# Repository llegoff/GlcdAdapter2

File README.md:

Smoothieboard-glcd-adapter v2
=============================
[See documentation on smoothiware.org](http://smoothieware.org/rrdglcdadapter)

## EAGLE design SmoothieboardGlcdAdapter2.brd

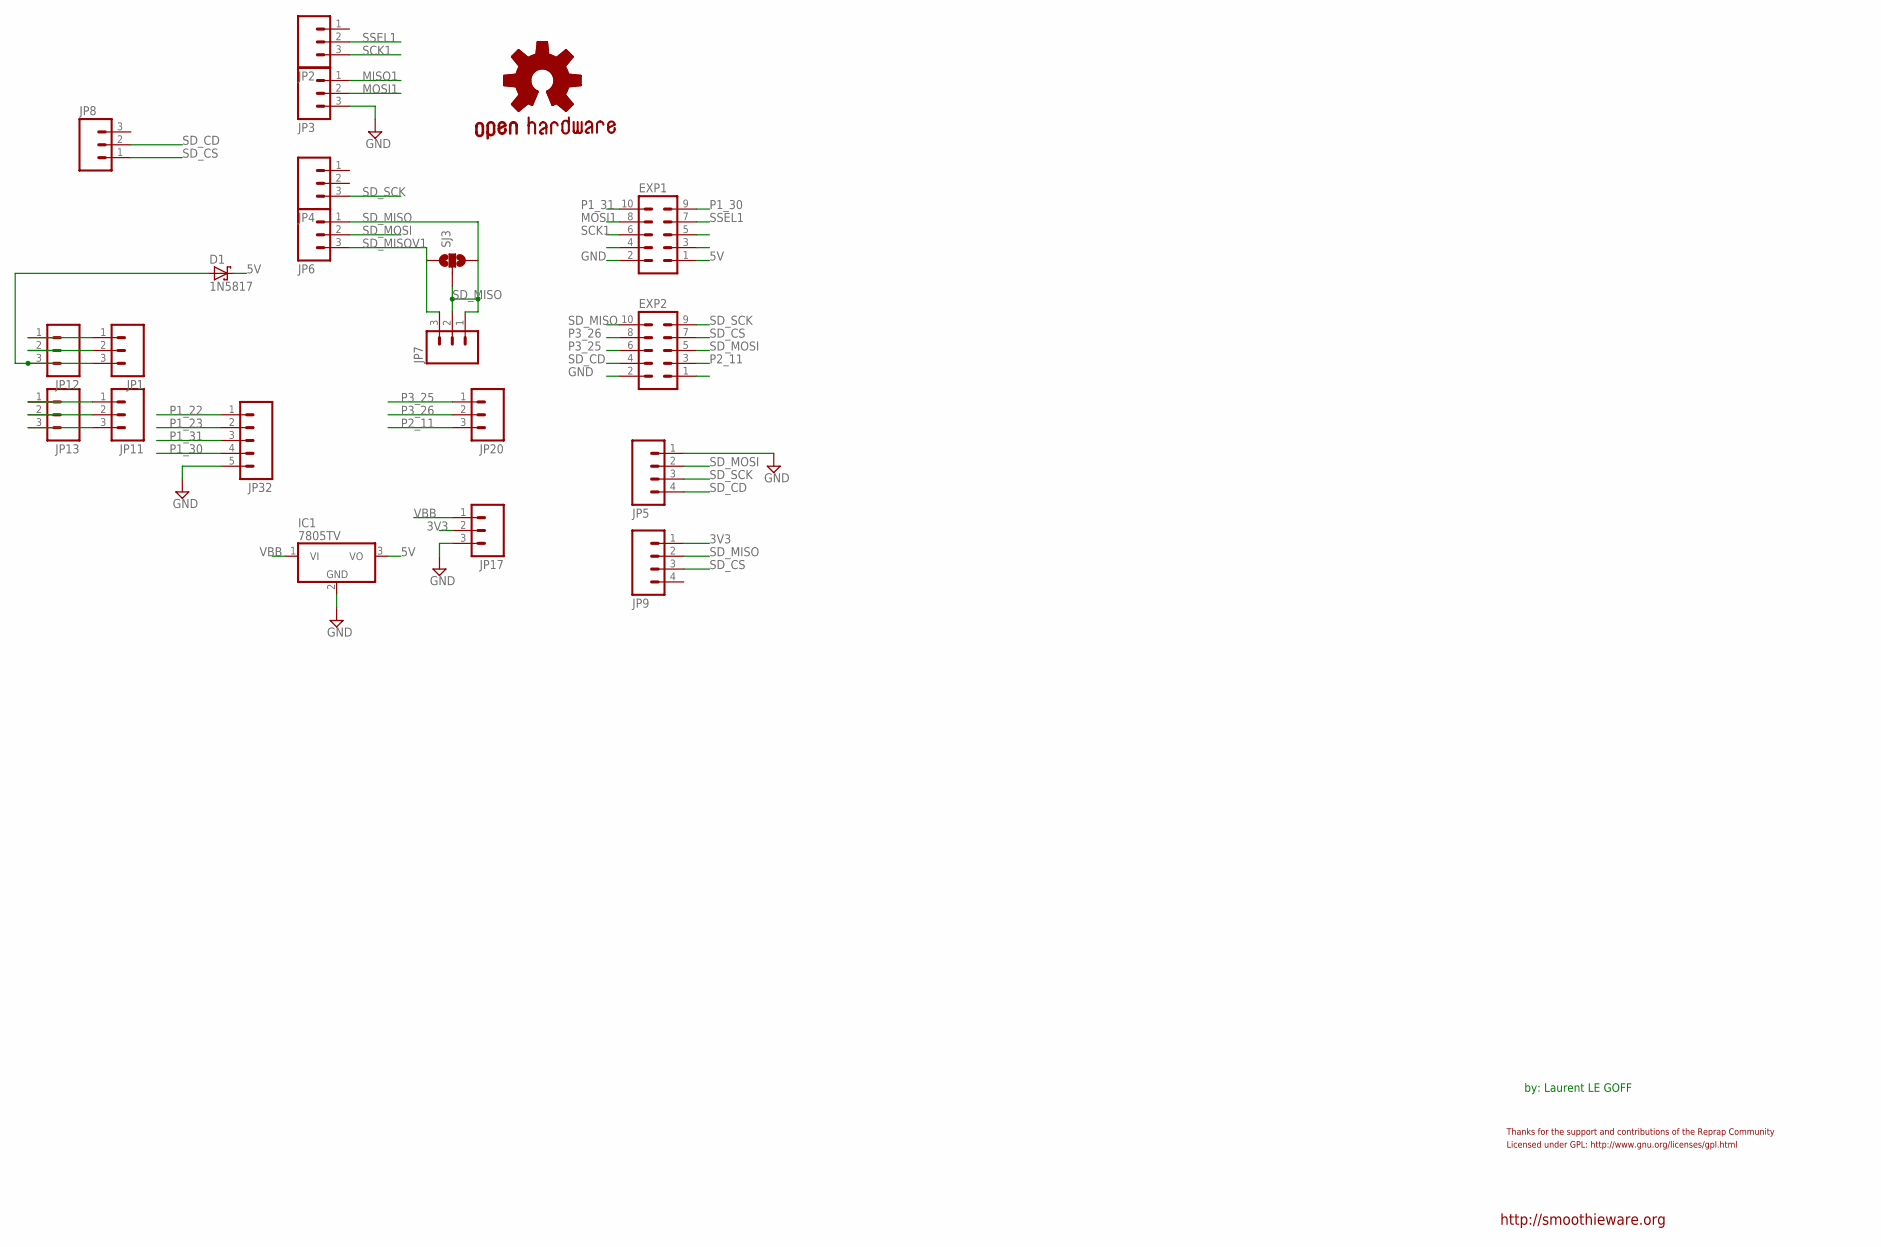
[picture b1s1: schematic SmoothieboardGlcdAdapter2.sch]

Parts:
D1: 1N5817; DO41-7.6
EXP1, EXP2: ML10
GOLD_ORB_SM1: OSHWLOGO_GOLD_ORB_MED; OSHW1
IC1: 7805TV; TO220V
JP1, JP7, JP8, JP11, JP12, JP13, JP17, JP20: M03PTH; 1X03
JP2, JP3, JP4, JP6: M031X03_NO_SILK; 1X03_NO_SILK
JP5, JP9: M041X04_NO_SILK; 1X04_NO_SILK
JP32: M05PTH; 1X05
SJ3: SOLDERJUMPER_2WAYS; SJ_3

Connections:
3V3: JP9.1, JP17.2
5V: D1.C, EXP1.1, IC1.3 (VO)
GND: EXP1.2, EXP2.2, IC1.2 (GND), JP3.3, JP5.1, JP17.3, JP32.5
MISO1: JP3.1
MOSI1: EXP1.8, JP3.2
unnamed: D1.A, JP1.3, JP12.3
unnamed: JP1.1, JP12.1
unnamed: JP1.2, JP12.2
unnamed: JP11.1, JP13.1
unnamed: JP11.2, JP13.2
unnamed: JP11.3, JP13.3
P1_22: JP32.1
P1_23: JP32.2
P1_30: EXP1.9, JP32.4
P1_31: EXP1.10, JP32.3
P2_11: EXP2.3, JP20.3
P3_25: EXP2.6, JP20.1
P3_26: EXP2.8, JP20.2
SCK1: EXP1.6, JP2.3
SD_CD: EXP2.4, JP5.4, JP8.2
SD_CS: EXP2.7, JP8.1, JP9.3
SD_MISO: EXP2.10, JP6.1, JP7.1, JP7.2, JP9.2, SJ3.2, SJ3.3
SD_MISOV1: JP6.3, JP7.3, SJ3.1
SD_MOSI: EXP2.5, JP5.2, JP6.2
SD_SCK: EXP2.9, JP4.3, JP5.3
SSEL1: EXP1.7, JP2.2
VBB: IC1.1 (VI), JP17.1

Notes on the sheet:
http://smoothieware.org
by: Laurent LE GOFF
Licensed under GPL: http://www.gnu.org/licenses/gpl.html
Thanks for the support and contributions of the Reprap Community

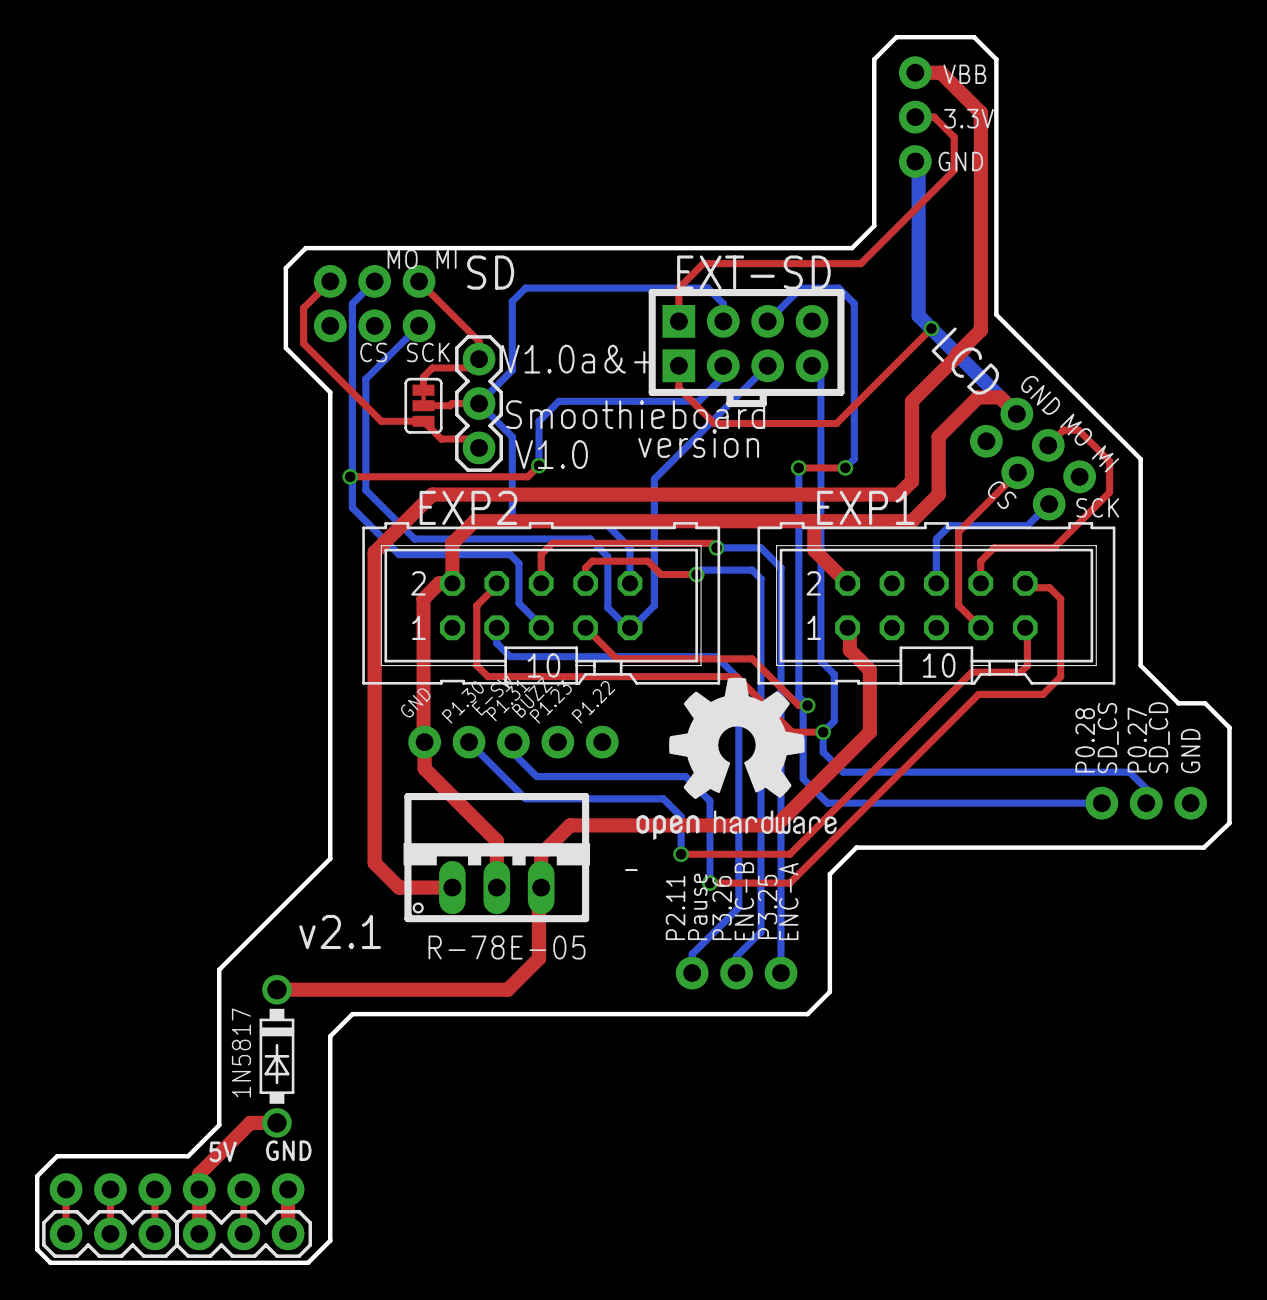
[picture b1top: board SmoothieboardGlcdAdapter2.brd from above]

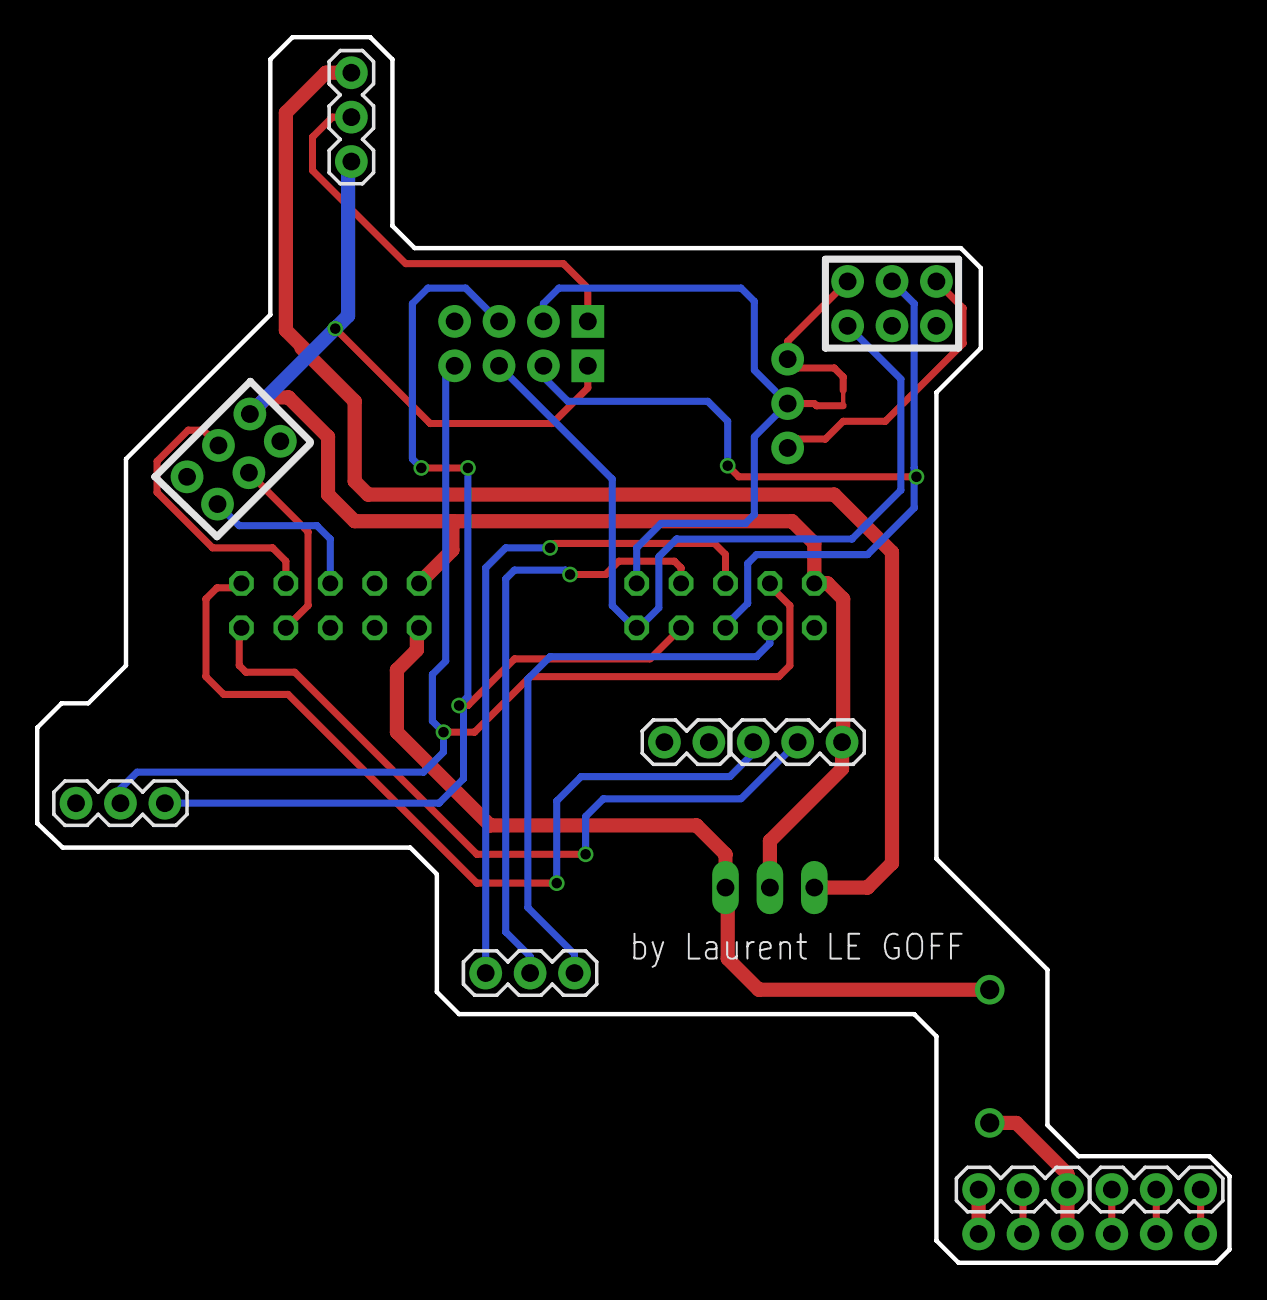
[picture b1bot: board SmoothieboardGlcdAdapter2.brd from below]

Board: 2 copper layers, 68.2 x 70.1 mm, 21 parts (6 on the bottom side), 24 nets.

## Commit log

2014-10-26 :octocat: Added .gitattributes
2014-11-04 label exp1 & exp2
2014-12-10 recom outline
2015-09-15 v2.1
